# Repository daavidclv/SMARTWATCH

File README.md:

# ⌚ Smartwatch — Diseño de PCB + Firmware

Diseño íntegro (hardware + firmware) de un smartwatch: esquemático, layout de PCB multicapa en KiCad y programación del microcontrolador.

## 📋 Descripción

Proyecto personal en el que desarrollé de principio a fin un dispositivo wearable, cubriendo tanto la parte de electrónica (diseño de PCB) como la de software embebido (firmware de control). El objetivo fue enfrentarme al ciclo completo de un producto electrónico: desde el esquemático hasta el código que corre en el propio dispositivo.

## 🛠️ Stack técnico

- **Diseño de PCB:** KiCad (esquemático + layout multicapa)
- **Firmware:** C/C++ (Arduino framework)
- **Hardware:** microcontrolador programado vía Arduino IDE

## 📁 Estructura del repositorio

- `final_v2.ino` — firmware principal del smartwatch
- `hardware.h` — definiciones de pines y configuración de hardware

> Nota: el esquemático y los archivos de PCB en KiCad se pueden añadir aquí como carpeta `/hardware` (o enlazar si se gestionan aparte).

## 📸 Resultado

**NO DISPONIBLE**
(Se lo llevo el profe :_( )

## 🎯 Lo más complejo del proyecto

- Diseño de PCB multicapa cuidando el tamaño reducido típico de un wearable
- Gestión de energía y periféricos desde el firmware con recursos limitados

## 👤 Autor

David Calvo Heredero — [LinkedIn](https://www.linkedin.com/in/david-calvo-heredero-20b20a33a) · [GitHub](https://github.com/daavidclv)

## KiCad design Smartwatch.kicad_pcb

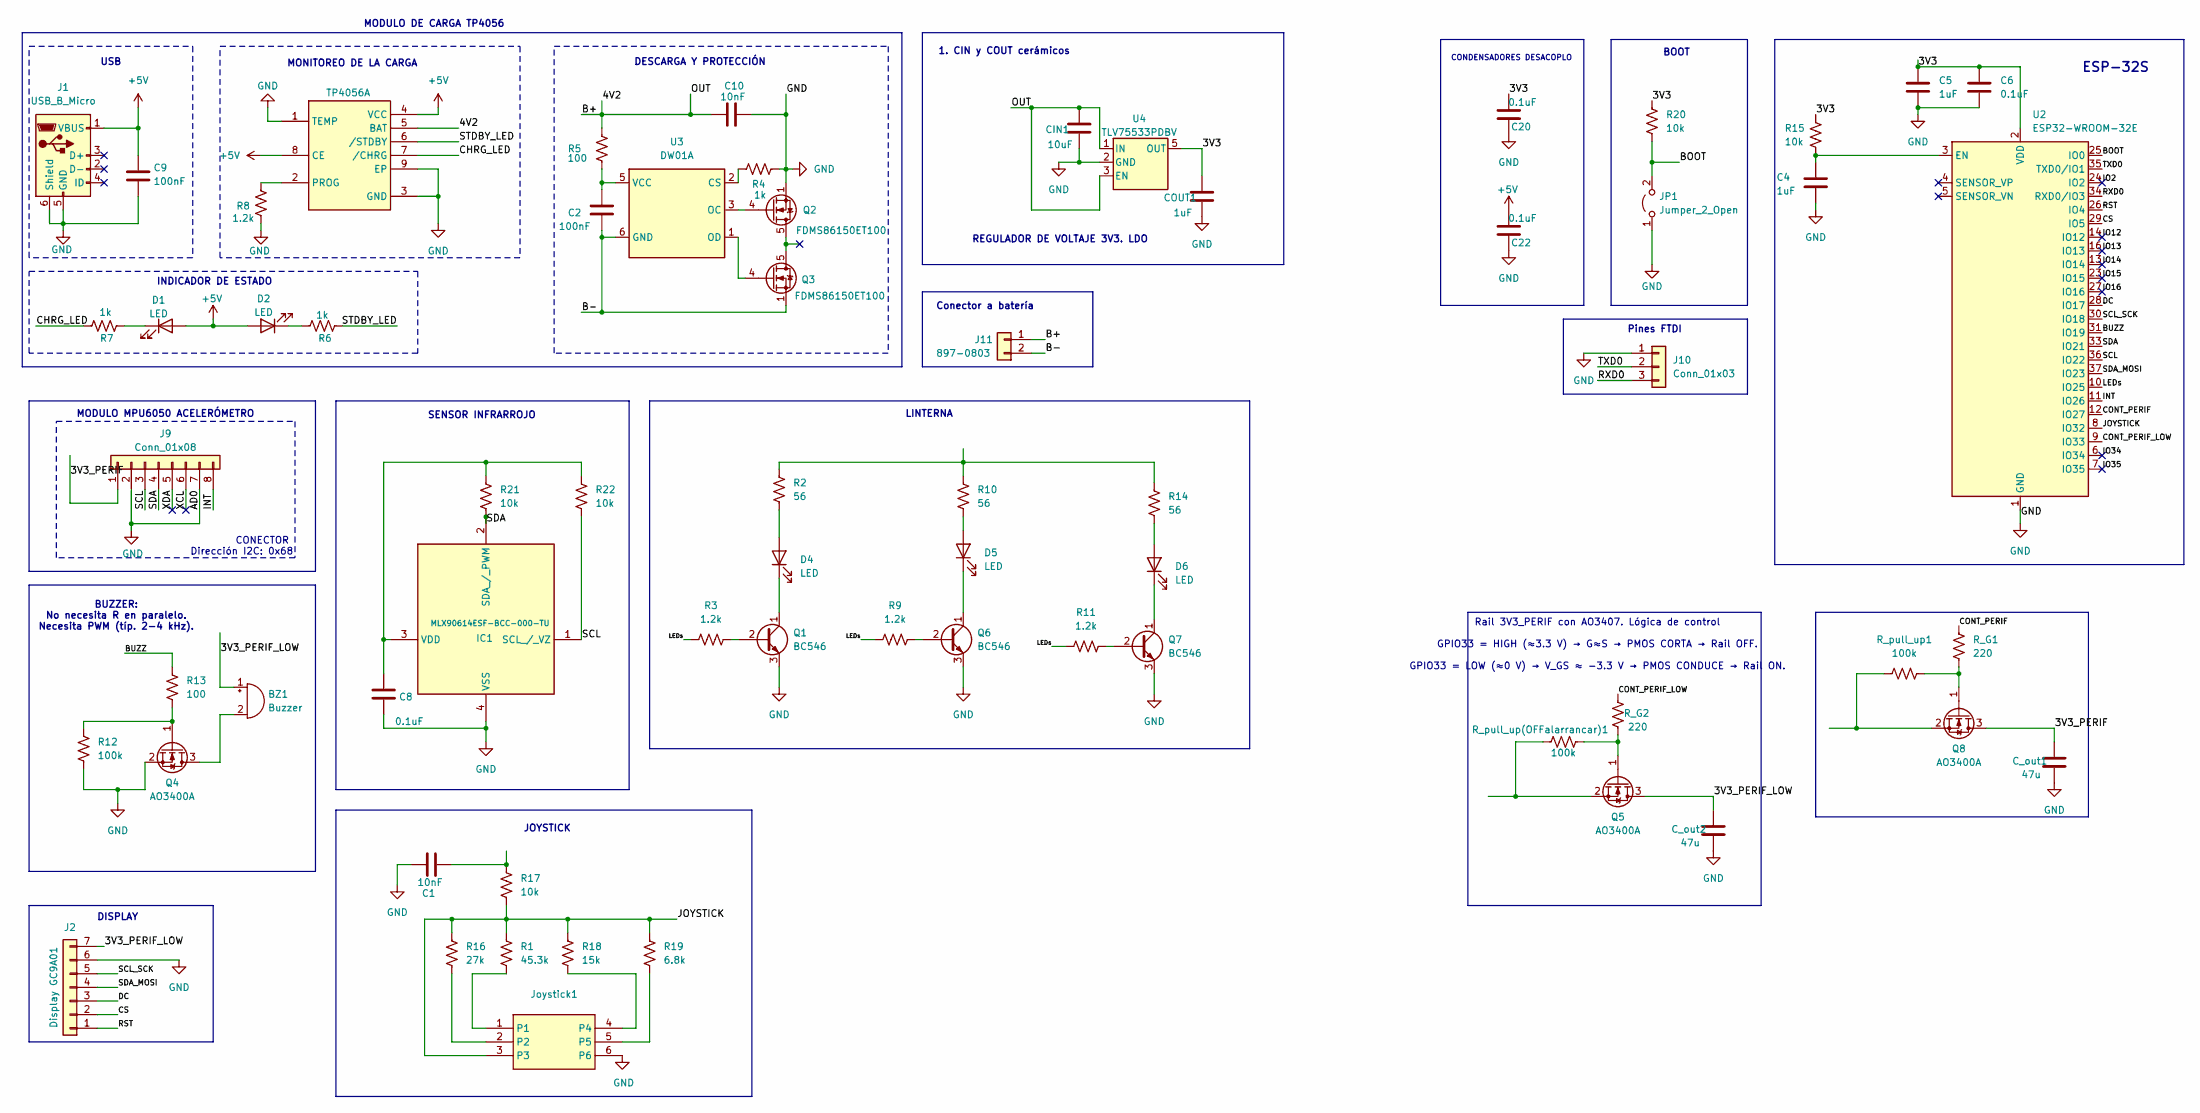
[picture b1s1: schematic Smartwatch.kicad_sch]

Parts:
BZ1: Buzzer; Buzzer_15x7.5RM7.6
C1, C10: 10nF; C_0805_2012Metric
C2, C9: 100nF; C_0805_2012Metric
C4, C5: 1uF; C_0805_2012Metric
C6, C8, C20, C22: 0.1uF; C_0805_2012Metric
CIN1: 10uF; CP_Radial_D4.0mm_P2.00mm
COUT1: 1uF; CP_Radial_D4.0mm_P2.00mm
C_out1, C_out2: 47u; C_0805_2012Metric
D1, D2, D4, D5, D6: LED; LED_D3.0mm
IC1: MLX90614ESF-BCC-000-TU; MLX90614ESFBCC000TU; Mouser Part Number 482-90614ESFBCC000TU
J1: USB_B_Micro; USB_Mini-B_Wuerth_65100516121_Horizontal
J2: Display GC9A01; PinHeader_1x07_P2.54mm_Vertical
J9: Conn_01x08; PinHeader_1x08_P2.54mm_Vertical
J10: Conn_01x03; PinHeader_1x03_P2.54mm_Vertical
J11: 897-0803; JST_XH_S2B-XH-A_1x02_P2.50mm_Horizontal
JP1: Jumper_2_Open; PinHeader_1x02_P2.54mm_Vertical
Joystick1: Joystick
Q1, Q6, Q7: BC546; TO-92_Inline
Q2, Q3: FDMS86150ET100; TDSON-8-1
Q4, Q5, Q8: AO3400A; SOT-23
R1: 45.3k; R_0805_2012Metric
R2, R10, R14: 56; R_0805_2012Metric
R3, R8, R9, R11: 1.2k; R_0805_2012Metric
R4, R6, R7: 1k; R_0805_2012Metric
R5, R13: 100; R_0805_2012Metric
R12: 100k; R_0805_2012Metric
R15, R17, R20, R21, R22: 10k; R_0805_2012Metric
R16: 27k; R_0805_2012Metric
R18: 15k; R_0805_2012Metric
R19: 6.8k; R_0805_2012Metric
R_G1, R_G2: 220; R_0805_2012Metric
R_pull_up1: 100k; R_0805_2012Metric
R_pull_up(OFFalarrancar)1: 100k; R_0805_2012Metric
TP4056: 4538; TP4056-42-ESOP8_TPW
U2: ESP32-WROOM-32E; ESP32-WROOM-32D
U3: DW01A; SOT-23-6
U4: TLV75533PDBV; SOT-23-5

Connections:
+5V: C9.1, C22.1, D1.2 (A), D2.2 (A), J1.1 (VBUS), TP4056.4 (VCC), TP4056.8 (CE)
/3V3: C5.1, C6.1, C20.1, COUT1.1, R15.1, R20.1, U2.2 (VDD), U4.5 (OUT)
/3V3_PERIF: C_out1.1, J9.1, Q8.3 (D)
/3V3_PERIF_LOW: BZ1.1 (+), C_out2.1, J2.7, Q5.3 (D)
/4V2: C10.1, CIN1.1, J11.1 (Puente1), R5.2, TP4056.5 (BAT), U4.1 (IN), U4.3 (EN)
/B-: C2.1, J11.2 (Puente2), Q3.1 (S), Q3.2 (S), Q3.3 (S), U3.6 (GND)
/BOOT: JP1.2 (B), R20.2, U2.25 (IO0)
/BUZZ: R13.2, U2.31 (IO19)
/CHRG_LED: R7.2, TP4056.7 (/CHRG)
/CONT_PERIF: R_G1.2, U2.12 (IO27)
/CONT_PERIF_LOW: R_G2.2, U2.9 (IO33)
/CS: J2.2, U2.29 (IO5)
/DC: J2.3, U2.28 (IO17)
/INT: J9.8, U2.11 (IO26)
/IO2: U2.24 (IO2)
/IO12: U2.14 (IO12)
/IO13: U2.16 (IO13)
/IO14: U2.13 (IO14)
/IO15: U2.23 (IO15)
/IO16: U2.27 (IO16)
/IO34: U2.6 (IO34)
/IO35: U2.7 (IO35)
/JOYSTICK: Joystick1.3, R1.1, R16.2, R17.1, R18.2, R19.2, U2.8 (IO32)
/LEDs: R3.1, R9.1, R11.1, U2.10 (IO25)
/RST: J2.1, U2.26 (IO4)
/RXD0: J10.3, U2.34 (RXD0/IO3)
/SCL: IC1.1 (SCL_/_VZ), J9.3, R22.2, U2.36 (IO22)
/SCL_SCK: J2.5, U2.30 (IO18)
/SDA: IC1.2 (SDA_/_PWM), J9.4, R21.1, U2.33 (IO21)
/SDA_MOSI: J2.4, U2.37 (IO23)
/STDBY_LED: R6.1, TP4056.6 (/STDBY)
/TXD0: J10.2, U2.35 (TXD0/IO1)
/XCL: J9.6
/XDA: J9.5
GND: C1.2, C4.2, C5.2, C6.2, C8.2, C9.2, C10.2, C20.2, C22.2, CIN1.2, COUT1.2, C_out1.2, C_out2.2, IC1.4 (VSS), J1.5 (GND), J1.6 (Shield), J2.6, J9.2, J9.7, J10.1, JP1.1 (A), Joystick1.6, Q1.3 (E), Q2.1 (S), Q2.2 (S), Q2.3 (S), Q4.2 (S), Q6.3 (E), Q7.3 (E), R4.2, R8.1, R12.1, TP4056.1 (TEMP), TP4056.3 (GND), TP4056.9 (EP), U2.1 (GND), U2.15 (GND), U2.38 (GND), U2.39 (GND), U4.2 (GND)
unnamed: BZ1.2 (-), Q4.3 (D)
unnamed: C1.1, R17.2
unnamed: D1.1 (K), R7.1
unnamed: D2.1 (K), R6.2
unnamed: D4.2 (A), R2.2
unnamed: D4.1 (K), Q1.1 (C)
unnamed: D5.2 (A), R10.2
unnamed: D5.1 (K), Q6.1 (C)
unnamed: D6.2 (A), R14.2
unnamed: D6.1 (K), Q7.1 (C)
unnamed: C8.1, IC1.3 (VDD), R21.2, R22.1
unnamed: Joystick1.1, R1.2
unnamed: Joystick1.2, R16.1
unnamed: Joystick1.4, R18.1
unnamed: Joystick1.5, R19.1
unnamed: Q1.2 (B), R3.2
unnamed: Q2.4 (G), U3.3 (OC)
unnamed: Q3.4 (G), U3.1 (OD)
unnamed: Q4.1 (G), R12.2, R13.1
unnamed 54: Q5.1 (G), R_G2.1, R_pull_up(OFFalarrancar)1.2; also elsewhere on the board
unnamed 55: Q5.2 (S), R_pull_up(OFFalarrancar)1.1; also elsewhere on the board
unnamed: Q6.2 (B), R9.2
unnamed: Q7.2 (B), R11.2
unnamed 58: Q8.1 (G), R_G1.1, R_pull_up1.2; also elsewhere on the board
unnamed 59: Q8.2 (S), R_pull_up1.1; also elsewhere on the board
unnamed: R2.1, R10.1, R14.1
unnamed: R8.2, TP4056.2 (PROG)
unnamed: C4.1, R15.2, U2.3 (EN)
unnamed: R4.1, U3.2 (CS)
unnamed: C2.2, R5.1, U3.5 (VCC)

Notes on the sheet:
CONECTOR
MODULO MPU6050 ACELERÓMETRO
DESCARGA Y PROTECCIÓN
USB
CONDENSADORES DESACOPLO
ESP-32S
Pines FTDI
SENSOR INFRARROJO
REGULADOR DE VOLTAJE 3V3. LDO
MODULO DE CARGA TP4056
Dirección I2C: 0x68
1. CIN y COUT cerámicos
LINTERNA
JOYSTICK
BUZZER: No necesita R en paralelo. Necesita PWM (típ. 2-4 kHz).
MONITOREO DE LA CARGA
DISPLAY
Rail 3V3_PERIF con AO3407. Lógica de control GPIO33 = HIGH (≈3.3 V) → G≈S → PMOS CORTA → Rail OFF. GPIO33 = LOW (≈0 V) → V_GS ≈ −3.3 V → PMOS CONDUCE → Rail ON.
Conector a batería
INDICADOR DE ESTADO
BOOT

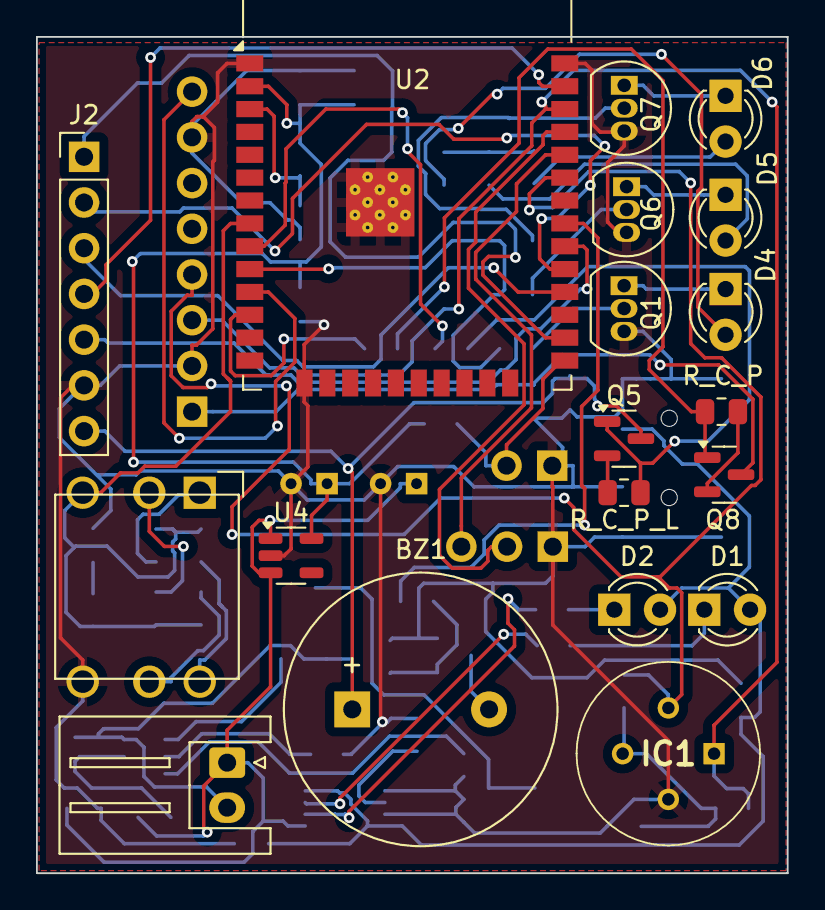
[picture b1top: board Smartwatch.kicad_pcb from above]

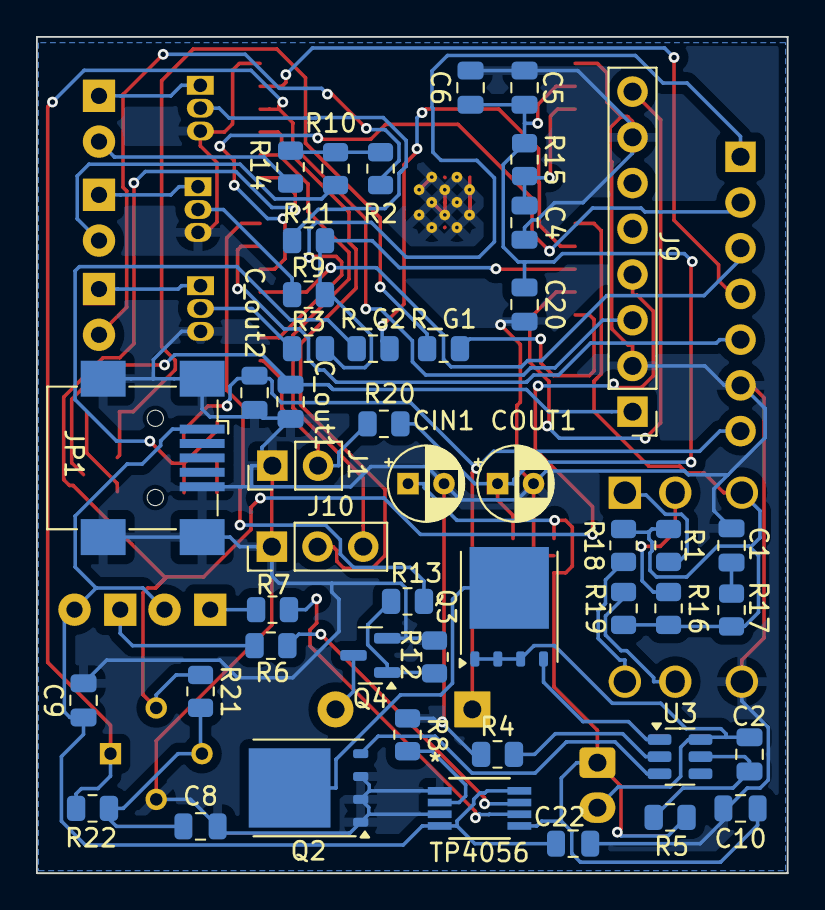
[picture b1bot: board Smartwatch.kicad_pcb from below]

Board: 2 copper layers, 41.7 x 46.5 mm, 66 parts (47 on the bottom side), 55 nets.

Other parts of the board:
R_C_P: 100k; R_0805_2012Metric
R_C_P_L: 100k; R_0805_2012Metric

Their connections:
unnamed 54: R_C_P_L.2; also elsewhere on the board
unnamed 55: R_C_P_L.1; also elsewhere on the board
unnamed 58: R_C_P.2; also elsewhere on the board
unnamed 59: R_C_P.1; also elsewhere on the board

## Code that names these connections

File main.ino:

/************************************************************
 *  WEARABLE ESP32 COMPLETO
 *  LCD + JOYSTICK + SENSORES + WEB + SPIFFS
 ************************************************************/

#include <Arduino.h>
#include "hardware.h"

/* ======== LIBRERÍAS ======== */
#include <WiFi.h>
#include <WebServer.h>
#include <SPIFFS.h>
#include <time.h>
#include <Wire.h>
#include <Adafruit_GFX.h>
#include <Adafruit_MLX90614.h>

/* ======== WIFI ======== */
#define WIFI_SSID "alvaro"
#define WIFI_PASS "12345678"

/* ======== WEB ======== */
WebServer server(80);


/* ======== SENSORES ======== */
Adafruit_MLX90614 mlx = Adafruit_MLX90614();

/* ======== VARIABLES GLOBALES ======== */
float currentTemperature = 0.0;
volatile int stepCount = 0;
bool linternaOn = false;

/* ======== SPIFFS ======== */
unsigned long ultimoGuardado = 0;
#define PERIODO_GUARDADO 60000UL


/* ======== PODÓMETRO ======== */
unsigned long lastStepSample = 0;
unsigned long lastStepTime = 0;
bool stepPossible = false;
#define STEP_SAMPLE_MS 50
#define STEP_DEBOUNCE_MS 300

/* ======== TEMPERATURA ======== */
unsigned long lastTempRead = 0;
#define TEMP_UPDATE_MS 1000

/* =========================================================
 *                       FUNCIONES
 * ========================================================= */

void initPeripheralRail() {
  pinMode(PIN_CONT_PERIF, OUTPUT);
  pinMode(PIN_CONT_PERIF_LOW, OUTPUT);
  digitalWrite(PIN_CONT_PERIF, HIGH);
  digitalWrite(PIN_CONT_PERIF_LOW, HIGH);
}

/* ---------- BATERÍA ---------- */
float readBattery() {
  int adc = analogRead(PIN_BAT_ADC);
  return adc * BAT_ADC_FACTOR * (3.3 / 4095.0);
}

/* ---------- HORA ---------- */
String getTimestamp() {
  time_t now;
  struct tm timeinfo;
  time(&now);
  if (!localtime_r(&now, &timeinfo)) return "1970-01-01 00:00:00";
  char buf[32];
  strftime(buf, sizeof(buf), "%Y-%m-%d %H:%M:%S", &timeinfo);
  return String(buf);
}

String getCurrentTime() {
  struct tm timeinfo;
  if (!getLocalTime(&timeinfo)) return "--:--";
  char buf[6];
  strftime(buf, sizeof(buf), "%H:%M", &timeinfo);
  return String(buf);
}

/* ---------- FLASH ---------- */
void guardarDatos() {
  int batPct = (int)(readBattery() / 4.2 * 100);
  String linea = getTimestamp() + "," +
                 String(stepCount) + "," +
                 String(currentTemperature,1) + "," +
                 String(batPct) + "\n";
  File f = SPIFFS.open("/datos.txt", FILE_APPEND);
  if (f) { f.print(linea); f.close(); }
}

// =====================
// ACTUADORES: LINTERNA Y ALARMA
// =====================

// Función para encender o apagar la linterna (LEDs discretos)
// Parámetro 'on': true -> encender linterna, false -> apagar
void setFlashlight(bool on) {
    flashlightOn = on;                         // Guardar estado actual
    digitalWrite(PIN_LEDS, on ? HIGH : LOW);  // Escribir en el pin correspondiente
    // HIGH = linterna encendida según tu esquema
    // LOW  = linterna apagada
}

// Inicialización del buzzer
void initBuzzer() {
    pinMode(PIN_BUZZER, OUTPUT);             // Configurar pin como salida
    ledcSetup(0, PWM_FREQ_BUZZ, 8);          // Configurar canal PWM 0, frecuencia definida, resolución 8 bits
    ledcAttachPin(PIN_BUZZER, 0);            // Asociar canal PWM al pin del buzzer
}

// Función que revisa la temperatura actual y enciende/apaga la linterna
// Se ejecuta periódicamente después de leer la temperatura
void checkTemperatureActuator() {
    if (currentTemperature > 30.0) {         // Si temperatura > 30°C
        setFlashlight(true);                 // Encender linterna
    } else {
        setFlashlight(false);                // Apagar linterna si temperatura <= 30°C
    }
}

// Función que revisa el estado de la batería y activa la alarma si baja del 50%
// La alarma se mantiene activa durante 5 segundos
void checkBatteryAlert() {
    float batteryPercent = readBattery() / 4.2 * 100; // Convertir voltaje a porcentaje

    // Si batería < 50% y alerta no estaba activa, iniciar temporizador
    if (batteryPercent < 50 && !batteryAlertActive) {
        batteryAlertStart = millis();       // Guardar tiempo de inicio
        batteryAlertActive = true;          // Marcar alerta como activa
    }

    // Si la alerta está activa, controlar duración del buzzer
    if (batteryAlertActive) {
        if (millis() - batteryAlertStart <= 5000) {  // Durante 5 segundos
            ledcWriteTone(0, PWM_FREQ_BUZZ);         // Activar buzzer
        } else {                                     // Después de 5 segundos
            ledcWriteTone(0, 0);                     // Apagar buzzer
            batteryAlertActive = false;              // Resetear bandera de alerta
        }
    }
}

/* =========================================================
 *                     WEB SERVER
 * ========================================================= */

const char MAIN_page[] PROGMEM = R"rawliteral(
<!DOCTYPE html><html><head><meta charset='utf-8'>
<title>Wearable ESP32</title></head><body>
<h2>Wearable</h2>
<p>Hora: <span id='t'></span></p>
<p>Batería: <span id='b'></span>%</p>
<p>Pasos: <span id='s'></span></p>
<p>Temp: <span id='tp'></span> °C</p>
<button onclick="fetch('/light/on')">Linterna ON</button>
<button onclick="fetch('/light/off')">Linterna OFF</button>
<a href='/datos'>Ver histórico</a>
<script>
setInterval(()=>{
fetch('/status').then(r=>r.json()).then(d=>{
t.innerText=d.time; b.innerText=d.battery;
s.innerText=d.steps; tp.innerText=d.temp;
});
},2000);
</script></body></html>
)rawliteral";

void handleRoot() {
  server.send(200, "text/html", MAIN_page);
}

void handleStatus() {
  int batPct = (int)(readBattery() / 4.2 * 100);
  String json = "{";
  json += "\"time\":\"" + getCurrentTime() + "\",";
  json += "\"battery\":" + String(batPct) + ",";
  json += "\"steps\":" + String(stepCount) + ",";
  json += "\"temp\":" + String(currentTemperature,1) + "}";
  server.send(200, "application/json", json);
}

void handleLightOn(){ setFlashlight(true); server.send(200); }
void handleLightOff(){ setFlashlight(false); server.send(200); }

void handleDatos() {
  String h="<pre>";
  File f = SPIFFS.open("/datos.txt", FILE_READ);
  while(f && f.available()) h+=(char)f.read();
  if(f)f.close();
  h+="</pre><a href='/'>Volver</a>";
  server.send(200,"text/html",h);
}

/* =========================================================
 *                     SENSORES
 * ========================================================= */

void updateTemperature() {
  if (millis() - lastTempRead < TEMP_UPDATE_MS) return;
  lastTempRead = millis();
  currentTemperature = mlx.readObjectTempC();
}

void updateStepCounter() {
  if (millis() - lastStepSample < STEP_SAMPLE_MS) return;
  lastStepSample = millis();

  int16_t ax, ay, az;
  Wire.beginTransmission(ADDR_MPU6050);
  Wire.write(0x3B);
  Wire.endTransmission(false);
  Wire.requestFrom(ADDR_MPU6050, 6, true);

  if (Wire.available() < 6) return;

  ax = Wire.read()<<8 | Wire.read();
  ay = Wire.read()<<8 | Wire.read();
  az = Wire.read()<<8 | Wire.read();

  float A = sqrt(pow(ax/16384.0,2)+pow(ay/16384.0,2)+pow(az/16384.0,2));

  if (A < 0.9) stepPossible = true;
  if (A > 1.2 && stepPossible && millis()-lastStepTime>STEP_DEBOUNCE_MS) {
    stepCount++;
    lastStepTime = millis();
    stepPossible = false;
  }
}


/* =========================================================
 *                     SETUP
 * ========================================================= */

void setup() {
  Serial.begin(115200);
  initPeripheralRail();

  pinMode(PIN_LEDS, OUTPUT);
  analogReadResolution(12);

  SPIFFS.begin(true);

  Wire.begin(I2C_SDA, I2C_SCL);
  Wire.beginTransmission(ADDR_MPU6050);
  Wire.write(0x6B); Wire.write(0);
  Wire.endTransmission();

  mlx.begin(ADDR_MLX90614, &Wire);


  WiFi.begin(WIFI_SSID, WIFI_PASS);
  while(WiFi.status()!=WL_CONNECTED) delay(200);

  configTime(0,0,"pool.ntp.org");
  setenv("TZ","CET-1CEST,M3.5.0,M10.5.0/3",1); tzset();

  server.on("/",handleRoot);
  server.on("/status",handleStatus);
  server.on("/light/on",handleLightOn);
  server.on("/light/off",handleLightOff);
  server.on("/datos",handleDatos);
  server.begin();

}

/* =========================================================
 *                     LOOP
 * ========================================================= */

void loop() {
  server.handleClient();
  updateTemperature();
  updateStepCounter();

  // Linterna y alarma
  checkTemperatureActuator();
  checkBatteryAlert();

  if (millis()-ultimoGuardado > PERIODO_GUARDADO) {
    guardarDatos();
    ultimoGuardado = millis();
  }
}
